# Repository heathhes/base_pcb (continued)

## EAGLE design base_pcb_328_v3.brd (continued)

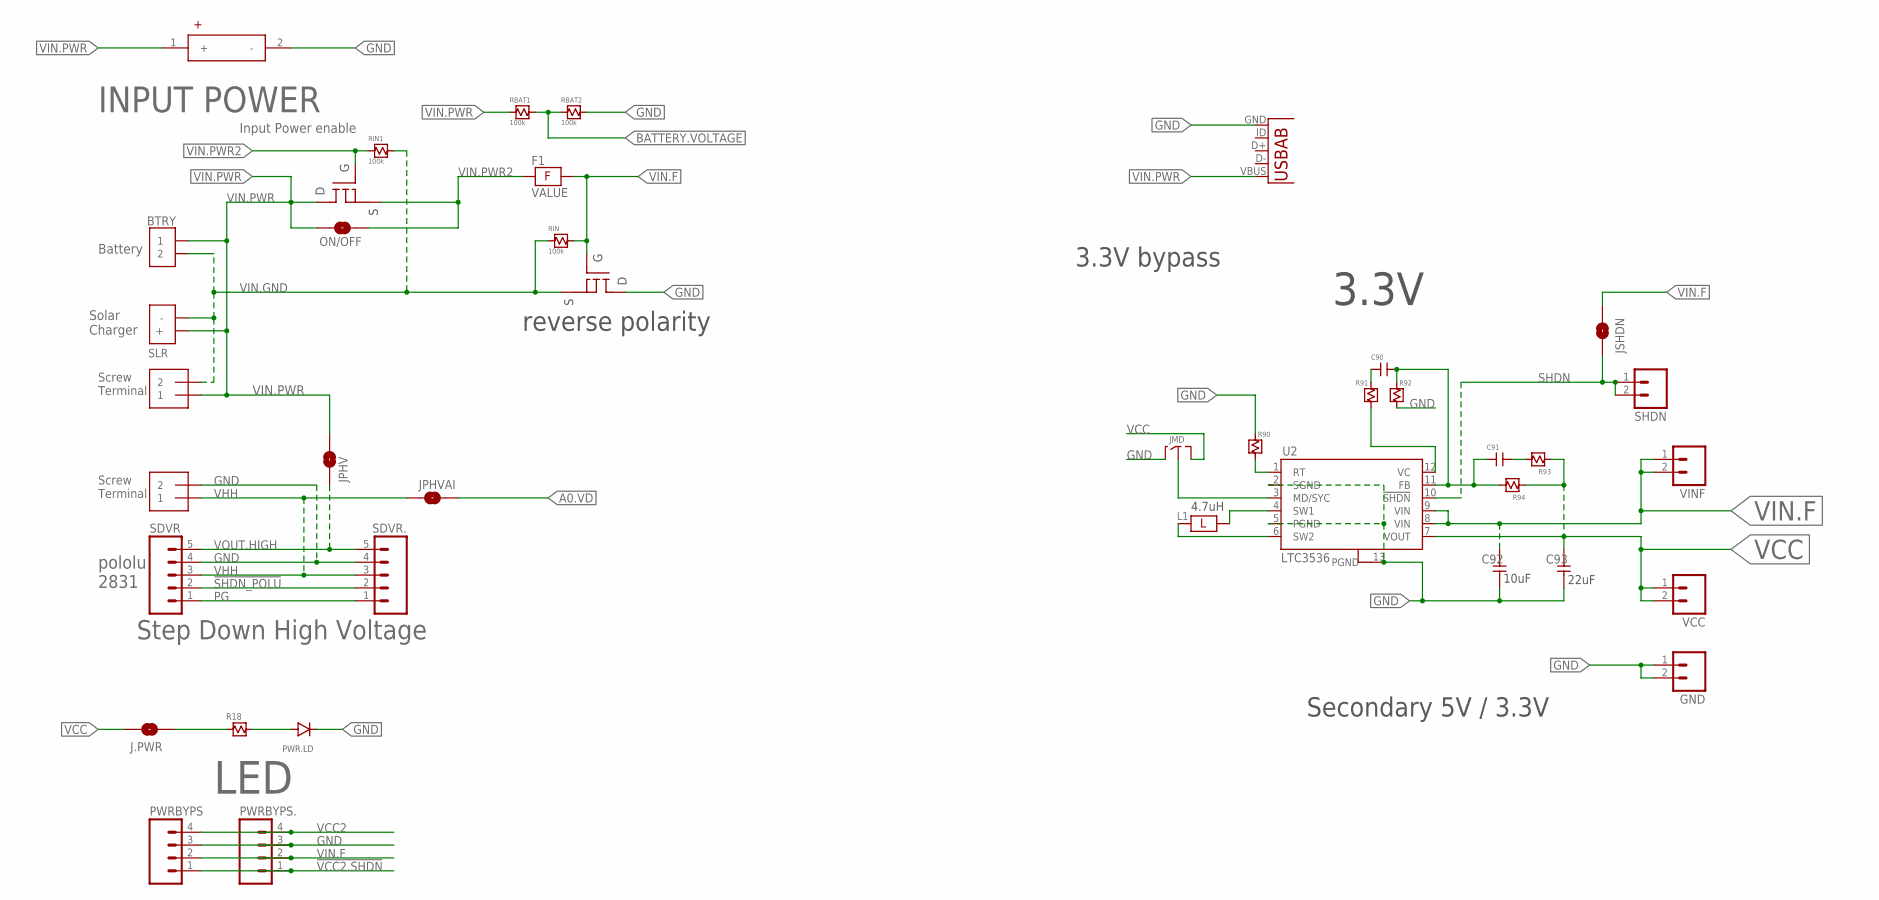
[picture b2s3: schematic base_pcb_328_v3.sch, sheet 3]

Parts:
BATTERY: BATTERY_HOLDER_18650
BTRY: MOLEX_2PIN_LOCKING_TH
C90, C91: 0603_CAPACITOR
C92: 10uF; 0805_CAPACITOR
C93: 22uF; 0805_CAPACITOR
F1: PTC_FUSE_PTC_1206; BEL_FUSE_PTC_FUSE_1206
GND: M02PTH; 1X02
INHPWR: 1X2-3.5MM
INPWR: 1X2-3.5MM
J.PWR: JUMPER-PAD-2-NOYES_SILK; PAD-JUMPER-2-NO_YES_SILK
JMD: JUMPER_3WAY_.1"_TH
JPHV: JUMPER-PAD-2-NOYES_SILK; PAD-JUMPER-2-NO_YES_SILK
JPHVAI: JUMPER-PAD-2-NOYES_SILK; PAD-JUMPER-2-NO_YES_SILK
JSHDN: JUMPER-PAD-2-NOYES_SILK; PAD-JUMPER-2-NO_YES_SILK
L1: 4.7uH; BOURNS_INDUCTOR_SMD
ON/OFF: JUMPER-PAD-2-NOYES_SILK; PAD-JUMPER-2-NO_YES_SILK
PWR.LD: 0603_LED
PWRBYPS, PWRBYPS.: M04PTH; 1X04
Q1, Q3: INFINEON_MOSFET_NCH; INFINEON_MOSFET_NCH_SMD
R18, R90, R91, R92, R93, R94: 0603_RESISTOR
RBAT1, RBAT2: 100k; 0603_RESISTOR
RIN, RIN1: 100k; 0603_RESISTOR
SDVR, SDVR.: M05PTH; 1X05
SHDN: M02PTH; 1X02
SLR: HEATH_SOLAR_CHARGER
U2: LTC3536_ADJ_12PIN
U4: USB-AB; USB-AB-MICRO-SMD
VCC: M02PTH; 1X02
VINF: M02PTH; 1X02

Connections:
!SHDN_POLU: SDVR.2, SDVR..2
!VCC2.SHDN: PWRBYPS.1, PWRBYPS..1
A0.VD: JPHVAI.1; also elsewhere on the board
BATTERY.VOLTAGE: RBAT1.2, RBAT2.1; also elsewhere on the board
GND: BATTERY.2 (-), C92.1, C93.1, GND.1, GND.2, INHPWR.2, JMD.P$3, PWR.LD.2, PWRBYPS.3, PWRBYPS..3, Q1.D, R90.2, R92.1, RBAT2.2, SDVR.4, SDVR..4, U2.2 (SGND), U2.5 (PGND), U2.13 (PGND), U4.GND; also elsewhere on the board
unnamed: L1.P$2, U2.4 (SW1)
unnamed: J.PWR.1, R18.1
unnamed: PWR.LD.1, R18.2
unnamed: L1.P$1, U2.6 (SW2)
unnamed: R90.1, U2.1 (RT)
unnamed: C90.2, C91.1, R92.2, R94.2, U2.11 (FB)
unnamed: C90.1, R91.2
unnamed: R91.1, U2.12 (VC)
unnamed: C91.2, R93.2
unnamed: JMD.P$2, U2.3 (MD/SYC)
PG: SDVR.1, SDVR..1
SHDN: JSHDN.2, SHDN.1, SHDN.2, U2.10 (!SHDN)
VCC: C93.2, J.PWR.2, JMD.P$1, R93.1, R94.1, U2.7 (VOUT), VCC.1, VCC.2; also elsewhere on the board
VCC2: PWRBYPS.4, PWRBYPS..4; also elsewhere on the board
VHH: INHPWR.1, JPHVAI.2, SDVR.3, SDVR..3
VIN.F: C92.2, F1.P$2, JSHDN.1, PWRBYPS.2, PWRBYPS..2, Q1.G, RIN.2, U2.8 (VIN), U2.9 (VIN), VINF.1, VINF.2
VIN.GND: BTRY.2, INPWR.2, Q1.S, RIN.1, RIN1.2, SLR.-
VIN.PWR: BATTERY.1 (+), BTRY.1, INPWR.1, JPHV.2, ON/OFF.1, Q3.D, RBAT1.1, SLR.+, U4.VBUS; also elsewhere on the board
VIN.PWR2: F1.P$1, ON/OFF.2, Q3.G, Q3.S, RIN1.1; also elsewhere on the board
VOUT.HIGH: JPHV.1, SDVR.5, SDVR..5

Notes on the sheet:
4.7uH
INPUT POWER
Battery
Solar Charger
Input Power enable
pololu 2831
Screw Terminal
Step Down High Voltage
LED
3.3V
3.3V bypass
Secondary 5V / 3.3V
reverse polarity

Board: 2 copper layers, 132 parts (0 on the bottom side), 84 nets, no tracks yet.

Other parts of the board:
U$1: POLYCASE_PCB_FOOTPRINT_5.5X4.1
U$3, U$10: PEM_2-56
U$8: BASE328_SHIELD_1

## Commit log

2019-10-18 initial repo commit, starts at v3.brd/sch/pro
2019-10-20 added first version
2019-10-20 updated to latest released and manufactured board
2019-11-23 removed old boms
2019-11-23 white space
